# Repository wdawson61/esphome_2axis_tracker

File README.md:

# Solar Tracker Complete System
## Dual-Axis Solar Tracker with Home Assistant Integration

**Version**: 1.0.0  
**Date**: November 2024  
**Hardware**: ESP32-C6 + WitMotion HWT905 + BTS7960 Motor Drivers

---

## 📦 What's Included

This complete package contains everything you need to build a professional dual-axis solar tracker:

### 🏠 Home Assistant Add-on
Professional Python application for intelligent tracking control:
- Astronomical sun position calculations
- 9-axis sensor fusion algorithms
- Dual-axis PID control
- Wind monitoring with Ecowitt integration
- Web dashboard and MQTT interface
- **Location**: `home_assistant_addon/solar_tracker/`

### 🔧 ESP32-C6 Firmware
Hardware controller for motors and sensors:
- WitMotion HWT905 IMU via RS485/Modbus
- BTS7960 43A motor driver control (4 PWM outputs)
- Dual-axis motion control (azimuth + elevation)
- Limit switch protection
- HTTP API for Home Assistant
- **Location**: `firmware/Solar_Tracker_ESP32C6_HWT905.ino`

### 📚 Complete Documentation
Detailed guides for every aspect:
- Hardware setup and wiring
- Firmware configuration and upload
- Home Assistant installation
- PID tuning and calibration
- Troubleshooting and maintenance
- **Location**: `docs/`

### 🔬 Example Code
Additional firmware options and references:
- Generic ESP32 firmware (non-C6 boards)
- ESPHome configuration
- Modbus communication examples
- **Location**: `examples/`

---

## 🎯 Your Hardware Configuration

### Core Components
- **MCU**: Seeed XIAO ESP32-C6
- **IMU**: WitMotion HWT905 (9-axis, RS485)
- **Motor Drivers**: 2× BTS7960 43A H-Bridge
- **Motors**: 
  - Azimuth: Slewing drive
  - Elevation: Linear actuator
- **Sensors**: 2× limit switches (East/West)
- **Weather**: Ecowitt WS90 (integrated in Home Assistant)

### Pin Configuration Summary
```
RS485:  D4(TX), D5(RX), D2(DE)
Azimuth Motor:  D8(RPWM), D9(LPWM)
Elevation Motor: D10(RPWM), D1(LPWM)
Limits: D6(East), D7(West)
```

Full details in: `docs/ESP32C6_HWT905_BTS7960_SETUP.md`

---

## 🚀 Quick Start Guide

### 1. Upload ESP32 Firmware (30 minutes)
```bash
1. Install Arduino IDE 2.x
2. Add ESP32 board support
3. Install ArduinoJson library
4. Open: firmware/Solar_Tracker_ESP32C6_HWT905.ino
5. Configure WiFi credentials
6. Select Board: XIAO_ESP32C6
7. Upload
8. Note IP address from Serial Monitor
```

**Detailed guide**: `docs/ESP32C6_HWT905_BTS7960_SETUP.md`

### 2. Wire Hardware (2-4 hours)
```bash
1. Connect RS485 board to HWT905 IMU
2. Wire BTS7960 driver #1 to azimuth motor
3. Wire BTS7960 driver #2 to elevation motor
4. Install limit switches
5. Connect power supplies (12-24V motors, 5V ESP32)
```

**Wiring diagrams**: `docs/ESP32C6_HWT905_BTS7960_SETUP.md` and `docs/WIRING.md`

### 3. Install Home Assistant Add-on (20 minutes)
```bash
1. Install Mosquitto MQTT broker (if not already)
2. Add this repository to Home Assistant
3. Install "Solar Tracker Controller" add-on
4. Configure:
   - ESP32 IP address
   - Your location (lat/long)
   - Ecowitt wind entities
   - PID parameters
5. Start add-on
```

**Detailed guide**: `home_assistant_addon/solar_tracker/INSTALL.md`

### 4. Test and Calibrate (1-2 hours)
```bash
1. Test IMU readings
2. Test motor movements
3. Verify limit switches
4. Configure wind monitoring
5. Calibrate sensors
6. Tune PID parameters
7. Test in manual mode
8. Enable auto mode
```

**Testing procedures**: `docs/ESP32C6_HWT905_BTS7960_SETUP.md`

---

## 📂 Directory Structure

```
solar_tracker_complete/
│
├── 📄 README.md                          ⭐ This file - Start here!
│
├── 📁 firmware/                          🔧 ESP32-C6 Firmware
│   └── Solar_Tracker_ESP32C6_HWT905.ino    Main firmware for your hardware
│
├── 📁 home_assistant_addon/              🏠 Home Assistant Add-on
│   └── solar_tracker/                      Complete add-on directory
│       ├── solar_tracker/                  Python application
│       │   ├── main.py                     Entry point
│       │   ├── controller.py               Main control logic
│       │   ├── sensor_fusion.py            9-axis IMU fusion
│       │   ├── esp32_interface.py          ESP32 communication
│       │   ├── mqtt_interface.py           MQTT integration
│       │   ├── ha_interface.py             HA entity reading
│       │   └── web_server.py               Web dashboard
│       ├── web/                            Web interface
│       │   └── index.html                  Dashboard UI
│       ├── config.yaml                     Add-on configuration
│       ├── Dockerfile                      Container build
│       ├── requirements.txt                Dependencies
│       ├── run.sh                          Startup script
│       ├── README.md                       Complete documentation
│       ├── INSTALL.md                      Installation guide
│       ├── QUICKSTART.md                   Quick reference
│       ├── ECOWITT_SETUP.md                Ecowitt WS90 integration
│       ├── HA_ENTITY_INTEGRATION.md        Entity integration guide
│       └── CHANGELOG.md                    Version history
│
├── 📁 docs/                              📚 Documentation
│   ├── ESP32C6_HWT905_BTS7960_SETUP.md   ⭐ PRIMARY HARDWARE GUIDE
│   ├── INDEX.md                            Master file index
│   ├── PROJECT_SUMMARY.md                  Executive overview
│   ├── AUTOMATION_VS_ADDON.md              Comparison guide
│   ├── WIRING.md                           Detailed wiring info
│   └── HARDWARE_GUIDE.md                   General hardware info
│
└── 📁 examples/                          🔬 Reference Code
    ├── ESP32_Modbus_Web_Original.ino       Your original RS485 code
    ├── ESP32_Modbus_Web.ino                Enhanced Modbus interface
    ├── Solar_Tracker_ESP32_Hardware.ino    Generic ESP32 firmware
    └── solar_tracker_esphome.yaml          ESPHome alternative
```

---

## 📖 Documentation Guide

### 🚀 Getting Started
1. **Start Here**: `README.md` (this file)
2. **Hardware Setup**: `docs/ESP32C6_HWT905_BTS7960_SETUP.md`
3. **Add-on Installation**: `home_assistant_addon/solar_tracker/INSTALL.md`
4. **Daily Operation**: `home_assistant_addon/solar_tracker/QUICKSTART.md`

### 🔧 Configuration
- **Wind Integration**: `home_assistant_addon/solar_tracker/ECOWITT_SETUP.md`
- **PID Tuning**: `docs/ESP32C6_HWT905_BTS7960_SETUP.md` (Calibration section)
- **Wiring Details**: `docs/WIRING.md` and `docs/ESP32C6_HWT905_BTS7960_SETUP.md`

### 📊 Reference
- **Complete File Index**: `docs/INDEX.md`
- **Project Overview**: `docs/PROJECT_SUMMARY.md`
- **Design Decisions**: `docs/AUTOMATION_VS_ADDON.md`

---

## 🎯 Key Features

### Astronomical Tracking
✅ Real-time sun position calculation (< 0.01° accuracy)  
✅ Automatic timezone handling  
✅ Dawn-to-dusk operation  
✅ Configurable stow position  

### Sensor Fusion
✅ 9-axis IMU (accelerometer + gyroscope + magnetometer)  
✅ Complementary filter algorithm  
✅ Tilt-compensated compass heading  
✅ Temperature compensation  
✅ Drift-free orientation tracking  

### Motor Control
✅ Dual-axis PID control (azimuth + elevation)  
✅ Smooth motion with configurable parameters  
✅ Anti-windup and output limiting  
✅ BTS7960 43A H-bridge drivers  
✅ 4 separate PWM outputs  

### Safety Features
✅ Wind monitoring with auto-stow (Ecowitt WS90)  
✅ Configurable wind threshold (average or gust)  
✅ Hardware limit switches (East/West)  
✅ Emergency stop  
✅ Communication watchdog  
✅ Automatic night stowing  

### Integration
✅ Home Assistant MQTT auto-discovery  
✅ Real-time web dashboard  
✅ RESTful API  
✅ Ecowitt weather station integration  
✅ Cloud-free operation  

---

## ⚙️ System Requirements

### Home Assistant Server
- Home Assistant OS, Supervised, or Container
- 2GB+ RAM recommended
- Mosquitto MQTT broker add-on
- Network access to ESP32

### ESP32 Hardware
- XIAO ESP32-C6 (or compatible)
- 5V power supply (2A)
- WiFi 2.4GHz network
- Stable IP address recommended

### Motors and Drivers
- 12V or 24V DC motors
- BTS7960 motor drivers (2×)
- Power supply sized for motor current
- Proper heat sinking

---

## 🔍 Troubleshooting

### Common Issues

**ESP32 won't connect to WiFi**
- Check SSID/password in firmware
- Ensure 2.4GHz network (not 5GHz)
- Check Serial Monitor for errors

**No IMU data**
- Verify RS485 wiring (A-to-A, B-to-B)
- Check HWT905 power and baud rate
- Test with `curl http://ESP_IP/api/sensors`

**Motors don't move**
- Check BTS7960 power (12-24V)
- Verify enable pins (R_EN, L_EN to 5V)
- Test PWM outputs with multimeter/oscilloscope
- Check motor connections (M+, M-)

**Add-on can't connect to ESP32**
- Verify ESP32 IP address
- Test with: `curl http://ESP_IP/status`
- Check firewall rules
- Ensure ESP32 web server is running

**Full troubleshooting guide**: `docs/ESP32C6_HWT905_BTS7960_SETUP.md`

---

## 📊 Performance Specifications

### Tracking Accuracy
- **Positioning**: ±0.5° - 1° (with tuned PID)
- **IMU Resolution**: 0.01° (HWT905)
- **Update Rate**: 10Hz (sensor reading), 1Hz (control loop)

### Efficiency Gains
- **vs Fixed Panel**: +30-35% energy production
- **vs Single-Axis**: +5-10% additional gain
- **Total Improvement**: 35-45% over fixed installation

### Response Time
- **Sun Tracking**: 15°/hour average motion
- **Motor Speed**: Configurable via PID
- **Typical**: Full range in 2-5 minutes

---

## 🛠️ Maintenance

### Regular Checks (Monthly)
- [ ] Clean solar panels
- [ ] Inspect mechanical components
- [ ] Check wire connections
- [ ] Verify limit switches
- [ ] Test emergency stop
- [ ] Review tracking logs

### Seasonal Tasks
- [ ] Recalibrate IMU (if drift detected)
- [ ] Re-tune PID parameters (if needed)
- [ ] Lubricate moving parts
- [ ] Check weatherproofing
- [ ] Update firmware/add-on

---

## 🆘 Support

### Documentation
- All guides included in `docs/` directory
- Add-on documentation in `home_assistant_addon/solar_tracker/`
- Hardware-specific info in `docs/ESP32C6_HWT905_BTS7960_SETUP.md`

### Self-Help
1. Check relevant documentation first
2. Review troubleshooting sections
3. Examine add-on logs in Home Assistant
4. Check ESP32 Serial Monitor output
5. Test individual components

### Creating Issues
When reporting problems, include:
- Hardware configuration
- Firmware version
- Add-on configuration (remove passwords)
- Complete error logs
- Steps to reproduce
- Photos of wiring (if applicable)

---

## 🎓 Learning Path

### Beginner (Week 1)
1. Upload firmware and test basic operation
2. Get familiar with web interface
3. Test manual motor control
4. Install Home Assistant add-on

### Intermediate (Week 2-3)
1. Configure wind monitoring
2. Calibrate IMU sensors
3. Basic PID tuning
4. Enable auto tracking for short periods

### Advanced (Week 4+)
1. Fine-tune PID parameters
2. Optimize for your location
3. Set up automations
4. Monitor and analyze performance
5. Customize code if needed

---

## 📜 License

This project is provided as-is for educational and personal use.

**Components**:
- Custom code: MIT License (modify freely)
- Hardware designs: Open source
- Documentation: Creative Commons

**Third-party libraries**:
- ArduinoJson: MIT License
- Home Assistant: Apache 2.0 License
- See individual files for specific licenses

---

## 🙏 Acknowledgments

**Hardware**:
- Seeed Studio (XIAO ESP32-C6)
- WitMotion (HWT905 IMU)
- BTS7960 driver manufacturers

**Software**:
- Home Assistant community
- Arduino/ESP32 ecosystem
- Python libraries

**Inspiration**:
- DIY solar tracking community
- Open source hardware movement

---

## 📈 Future Enhancements

### Planned Features (v1.1+)
- [ ] Cloud cover detection
- [ ] Historical performance tracking
- [ ] Machine learning for predictive control
- [ ] Multi-tracker coordination
- [ ] Mobile app integration
- [ ] Weather forecast integration

### Community Contributions Welcome
- Additional hardware support
- Improved algorithms
- Better documentation
- Language translations

---

## 🎉 You're Ready to Build!

**What you have**:
✅ Professional dual-axis firmware  
✅ Intelligent Home Assistant add-on  
✅ Complete documentation  
✅ Hardware-specific setup guide  
✅ Troubleshooting resources  
✅ Example code and references  

**Time to build**: ~1-2 days for complete setup  
**Cost**: ~$300-500 for electronics + motors  
**Result**: Professional solar tracker with 35-45% efficiency gain!

---

## 📞 Quick Reference

| Component | Location | Purpose |
|-----------|----------|---------|
| **Firmware** | `firmware/Solar_Tracker_ESP32C6_HWT905.ino` | Upload to ESP32 |
| **Setup Guide** | `docs/ESP32C6_HWT905_BTS7960_SETUP.md` | Hardware instructions |
| **Add-on** | `home_assistant_addon/solar_tracker/` | Install in HA |
| **Install Guide** | `home_assistant_addon/solar_tracker/INSTALL.md` | HA setup |
| **Quick Ref** | `home_assistant_addon/solar_tracker/QUICKSTART.md` | Daily operation |
| **Wind Setup** | `home_assistant_addon/solar_tracker/ECOWITT_SETUP.md` | Ecowitt config |
| **Examples** | `examples/` | Reference code |

---

**Happy Tracking! 🌞**

For the most up-to-date information, always refer to the documentation in the `docs/` directory.

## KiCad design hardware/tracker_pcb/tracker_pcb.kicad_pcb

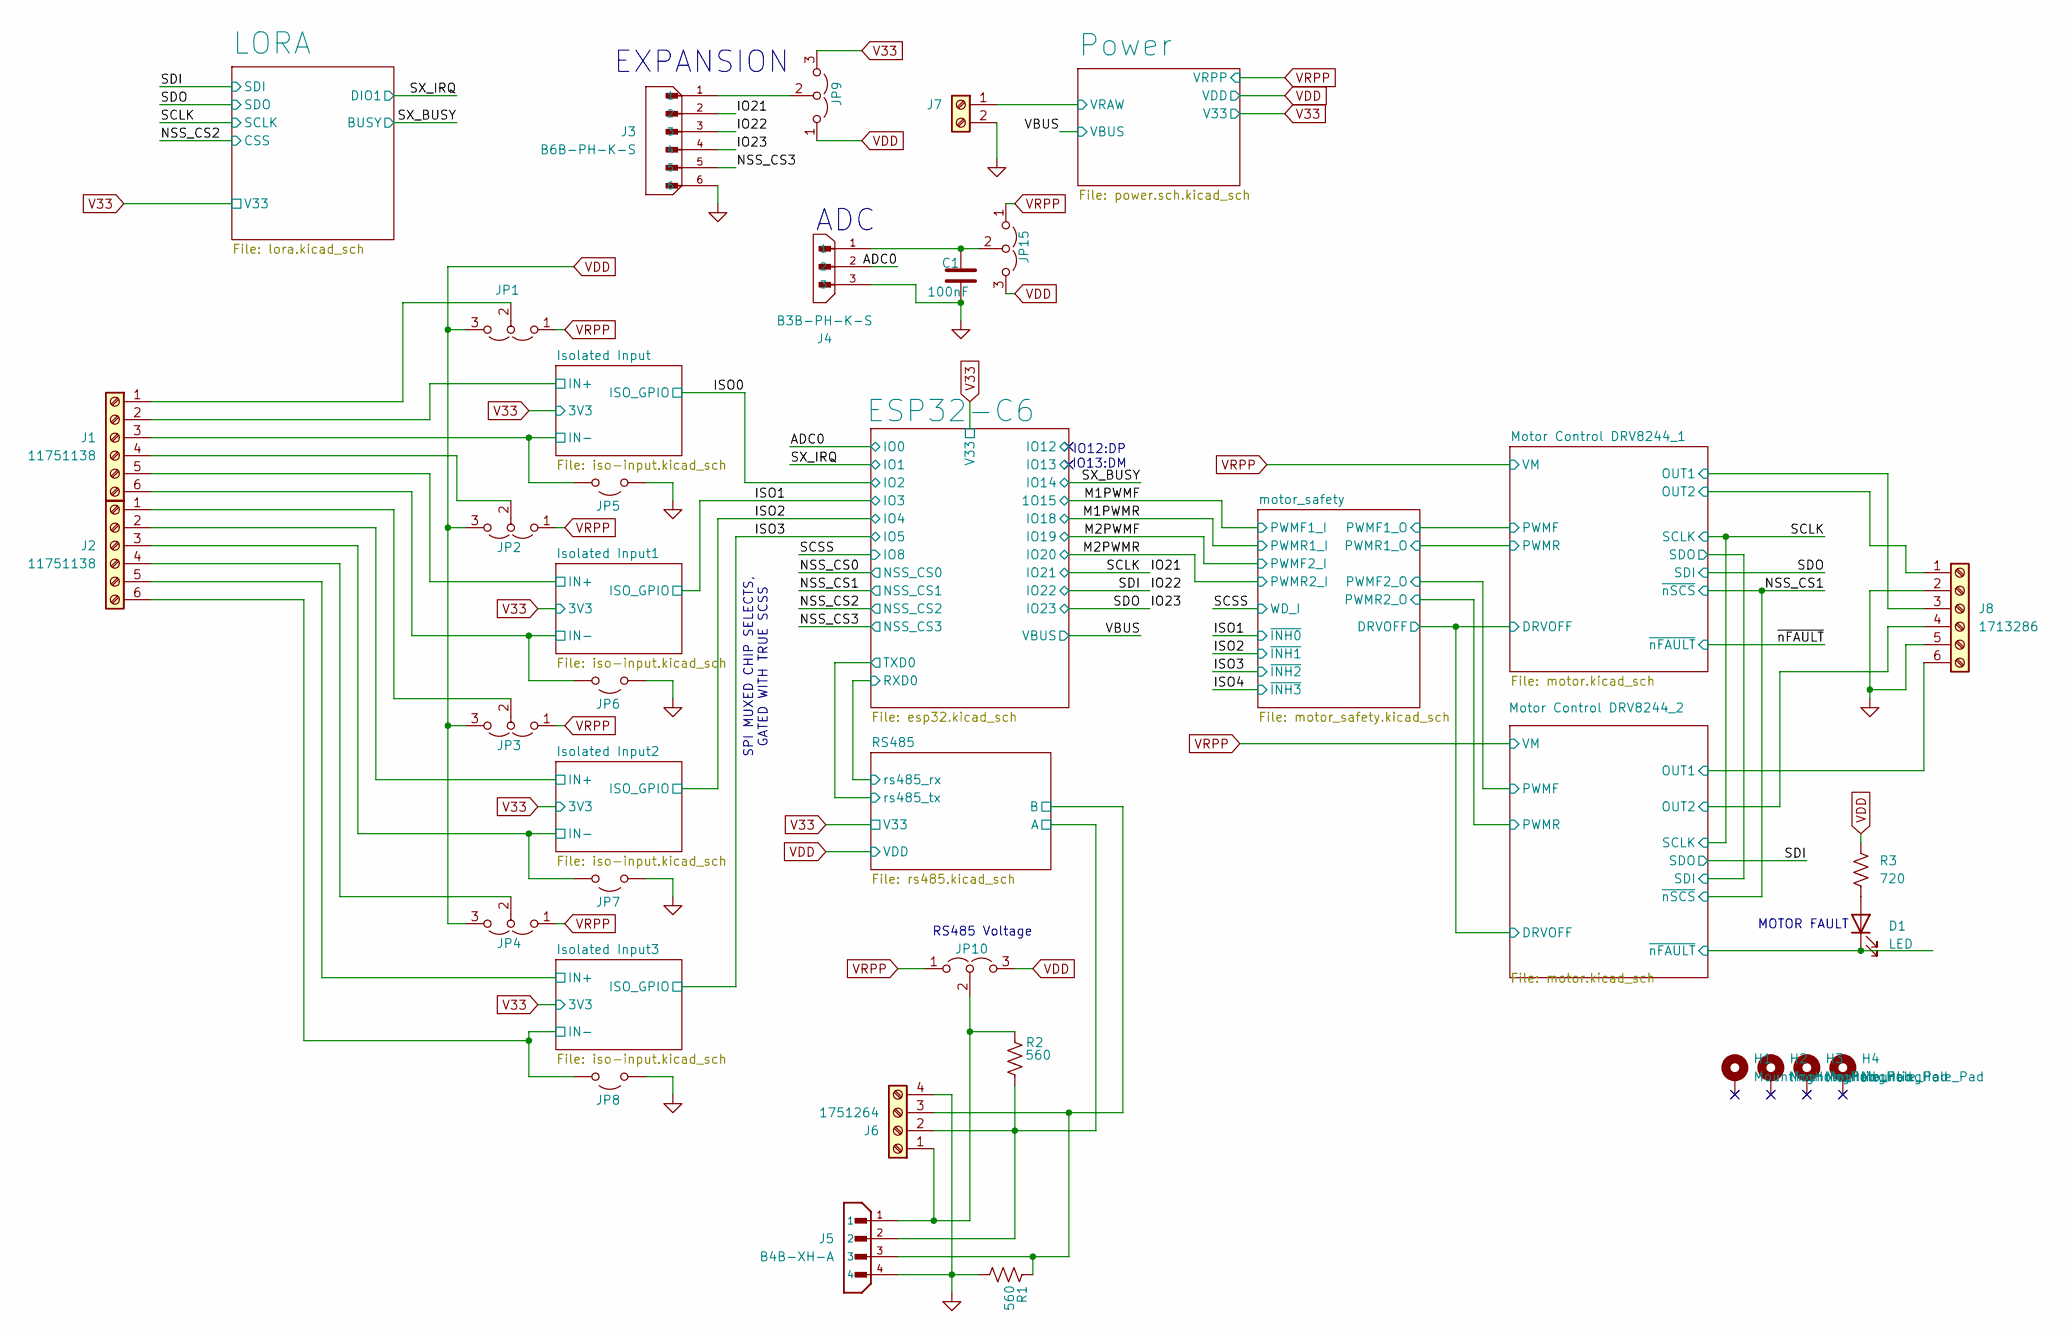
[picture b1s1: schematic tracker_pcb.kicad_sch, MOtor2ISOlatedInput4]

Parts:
C1: 100nF; C_0402_1005Metric; LCSC C1525
D1: LED; LED_0603_1608Metric; LCSC C12624
H1, H2, H3, H4: MountingHole_Pad; MountingHole_3.5mm_Pad_Via
J1, J2: 11751138; CONN_1751138_PXC; LCSC C2997513
J3: B6B-PH-K-S; JST_B6B-PH-K-S; LCSC C131342
J4: B3B-PH-K-S; JST_B3B-PH-K-S
J5: B4B-XH-A; JST_B4B-XH-A; PARTREV 7/4/21
J6: 1751264; PHOENIX_1751264; LCSC C99845
J7: Screw_Terminal_01x02; CONN_1720033_PXC; LCSC C5137859
J8: 1713286; PHOENIX_1905120; LCSC C2997523
JP1, JP2, JP3, JP4, JP9, JP10, JP15: Jumper_3_Open; PinHeader_1x03_P2.00mm_Vertical; LCSC C265013
JP5, JP6, JP7, JP8: Jumper_2_Open; PinHeader_1x02_P2.00mm_Vertical; LCSC C160332
R1, R2: 560; R_0603_1608Metric
R3: 720; R_0603_1608Metric; LCSC C23179

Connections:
/ADC0: J4.2; also elsewhere on the board
/IO21: J3.2; also elsewhere on the board
/IO22: J3.3; also elsewhere on the board
/IO23: J3.4; also elsewhere on the board
/Isolated Input1/IN+: J1.5; also elsewhere on the board
/Isolated Input1/IN-: J1.6, JP6.2 (B); also elsewhere on the board
/Isolated Input2/IN+: J2.2; also elsewhere on the board
/Isolated Input2/IN-: J2.3, JP7.2 (B); also elsewhere on the board
/Isolated Input3/IN+: J2.5; also elsewhere on the board
/Isolated Input3/IN-: J2.6, JP8.2 (B); also elsewhere on the board
/Isolated Input/IN+: J1.2; also elsewhere on the board
/Isolated Input/IN-: J1.3, JP5.2 (B); also elsewhere on the board
/Motor Control DRV8244_1/OUT1: J8.3; also elsewhere on the board
/Motor Control DRV8244_1/OUT2: J8.1; also elsewhere on the board
/Motor Control DRV8244_2/OUT1: J8.6; also elsewhere on the board
/Motor Control DRV8244_2/OUT2: J8.4; also elsewhere on the board
/Motor Control DRV8244_2/~nFAULT: D1.1 (K); also elsewhere on the board
/NSS_CS3: J3.5; also elsewhere on the board
/Power/VRAW: J7.1; also elsewhere on the board
/RS485/A: J5.2, J6.2, R2.1; also elsewhere on the board
/RS485/B: J5.3, J6.3, R1.2; also elsewhere on the board
GND: C1.2, J3.6, J4.3, J5.4, J6.4, J7.2, J8.2, J8.5, JP5.1 (A), JP6.1 (A), JP7.1 (A), JP8.1 (A), R1.1; also elsewhere on the board
unnamed: D1.2 (A), R3.1
unnamed: J1.1, JP1.2 (C)
unnamed: J1.4, JP2.2 (C)
unnamed: J2.1, JP3.2 (C)
unnamed: J2.4, JP4.2 (C)
unnamed: J3.1, JP9.2 (C)
unnamed: J5.1, J6.1, JP10.2 (C), R2.2
unnamed: C1.1, J4.1, JP15.2 (C)
V33: JP9.3 (B); also elsewhere on the board
VDD: JP1.3 (B), JP2.3 (B), JP3.3 (B), JP4.3 (B), JP9.1 (A), JP10.3 (B), JP15.3 (B), R3.2; also elsewhere on the board
VRPP: JP1.1 (A), JP2.1 (A), JP3.1 (A), JP4.1 (A), JP10.1 (A), JP15.1 (A); also elsewhere on the board

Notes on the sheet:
SPI MUXED CHIP SELECTS, GATED WITH TRUE SCSS
MOTOR FAULT
RS485 Voltage
IO12:DP IO13:DM
EXPANSION
ADC

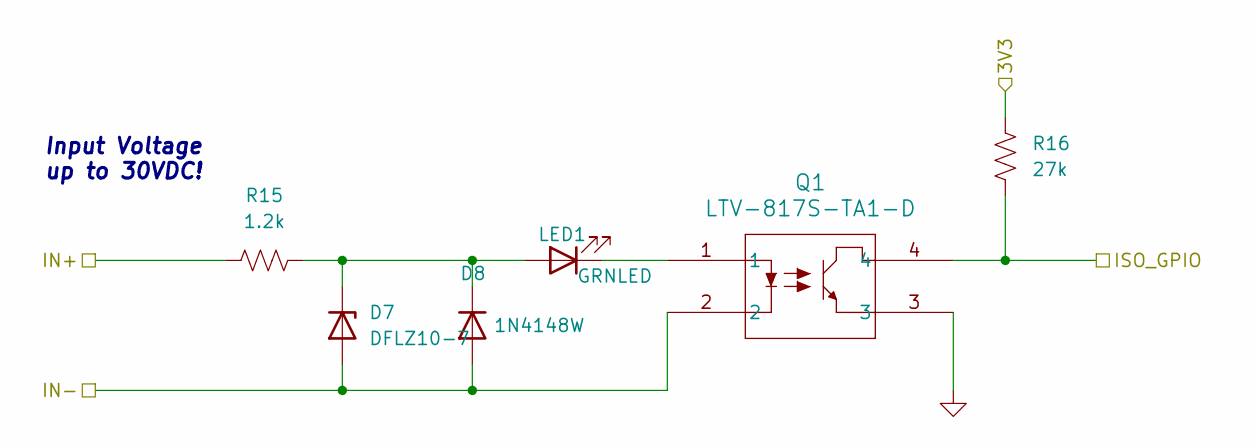
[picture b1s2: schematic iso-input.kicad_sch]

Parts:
D7: DFLZ10-7; DFLZ107; LCSC Part Name DFLZ10-7
D8: 1N4148W; D_SOD-323; LCSC C81598
LED1: GRNLED; LED_0603_1608Metric; LCSC C2288
Q1: LTV-817S-TA1-D; LTV-817S_LTO; LCSC C114603
R15: 1.2k; R_2010_5025Metric; LCSC C2078103
R16: 27k; R_0603_1608Metric; LCSC C22967

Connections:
/ISO0: Q1.4, R16.2; also elsewhere on the board
/Isolated Input/IN+: R15.1; also elsewhere on the board
/Isolated Input/IN-: D7.2 (A), D8.2 (A), Q1.2; also elsewhere on the board
GND: Q1.3; also elsewhere on the board
unnamed: D7.1 (K), D8.1 (K), LED1.2 (A), R15.2
unnamed: LED1.1 (K), Q1.1
V33: R16.1; also elsewhere on the board

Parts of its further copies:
D9, D11, D13: DFLZ10-7; DFLZ107; LCSC Part Name DFLZ10-7
D10, D12, D14: 1N4148W; D_SOD-323; LCSC C81598
LED2, LED3, LED4: GRNLED; LED_0603_1608Metric; LCSC C2288
Q2, Q3, Q4: LTV-817S-TA1-D; LTV-817S_LTO; LCSC C114603
R17, R19, R21: 1.2k; R_2010_5025Metric; LCSC C2078103
R18, R20, R22: 27k; R_0603_1608Metric; LCSC C22967

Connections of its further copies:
/ISO1: Q2.4, R18.2; also elsewhere on the board
/ISO2: Q3.4, R20.2; also elsewhere on the board
/ISO3: Q4.4, R22.2; also elsewhere on the board
/Isolated Input1/IN+: R17.1; also elsewhere on the board
/Isolated Input1/IN-: D9.2 (A), D10.2 (A), Q2.2; also elsewhere on the board
/Isolated Input2/IN+: R19.1; also elsewhere on the board
/Isolated Input2/IN-: D11.2 (A), D12.2 (A), Q3.2; also elsewhere on the board
/Isolated Input3/IN+: R21.1; also elsewhere on the board
/Isolated Input3/IN-: D13.2 (A), D14.2 (A), Q4.2; also elsewhere on the board
GND: Q2.3, Q3.3, Q4.3; also elsewhere on the board
unnamed: D9.1 (K), D10.1 (K), LED2.2 (A), R17.2
unnamed: D11.1 (K), D12.1 (K), LED3.2 (A), R19.2
unnamed: D13.1 (K), D14.1 (K), LED4.2 (A), R21.2
unnamed: LED2.1 (K), Q2.1
unnamed: LED3.1 (K), Q3.1
unnamed: LED4.1 (K), Q4.1
V33: R18.1, R20.1, R22.1; also elsewhere on the board

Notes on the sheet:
Input Voltage up to 30VDC!

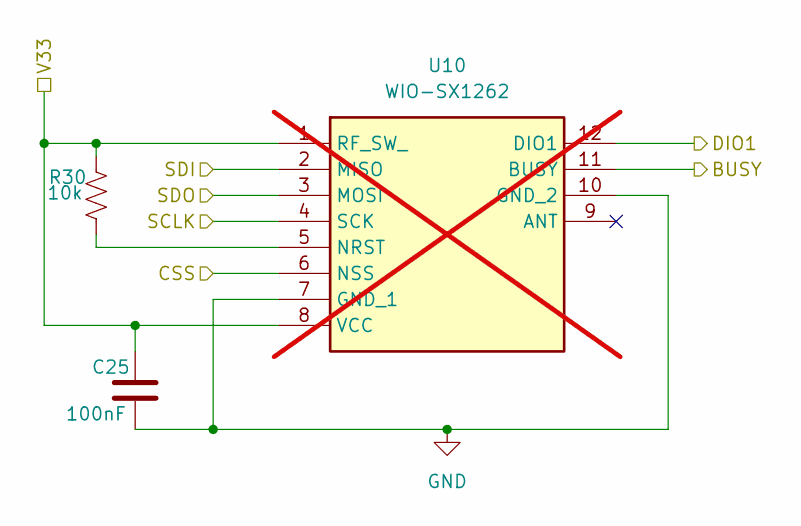
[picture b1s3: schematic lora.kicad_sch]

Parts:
C25: 100nF; C_0603_1608Metric; LCSC C1590
R30: 10k; R_0805_2012Metric; LCSC C17414
U10: WIO-SX1262; 114993390; Mouser Part Number 713-114993390; not fitted

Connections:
/IO21: U10.4 (SCK); also elsewhere on the board
/IO22: U10.2 (MISO); also elsewhere on the board
/IO23: U10.3 (MOSI); also elsewhere on the board
/NSS_CS2: U10.6 (NSS); also elsewhere on the board
/SX_BUSY: U10.11 (BUSY); also elsewhere on the board
/SX_IRQ: U10.12 (DIO1); also elsewhere on the board
GND: C25.2, U10.7 (GND_1), U10.10 (GND_2); also elsewhere on the board
unnamed: R30.2, U10.5 (NRST)
V33: C25.1, R30.1, U10.1 (RF_SW_), U10.8 (VCC); also elsewhere on the board

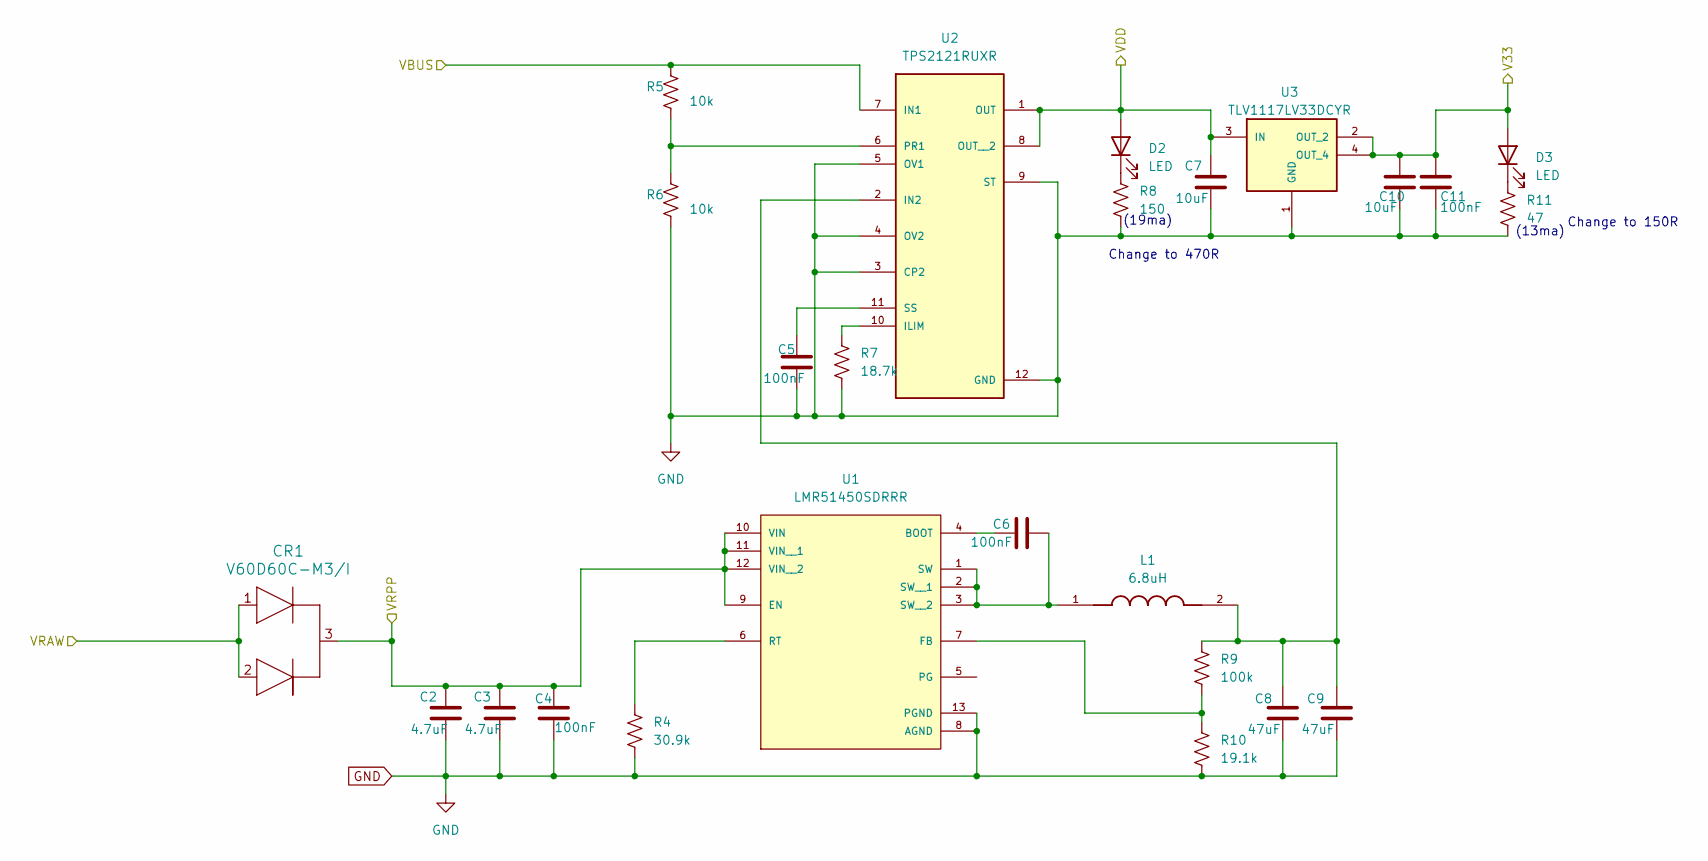
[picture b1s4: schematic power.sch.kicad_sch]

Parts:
C2, C3: 4.7uF; C_1206_3216Metric; LCSC C77096
C4, C6, C11: 100nF; C_0603_1608Metric; LCSC C1590
C5: 100nF; C_0402_1005Metric; LCSC C1525
C7, C10: 10uF; C_1206_3216Metric; LCSC C1849
C8, C9: 47uF; C_1210_3225Metric; LCSC C77101
CR1: V60D60C-M3/I; DPAK_60C-M3&slash_I_VIS; LCSC C3759778
D2, D3: LED; LED_0603_1608Metric; LCSC C12624
L1: 6.8uH; IND_XAL6060-682MEC; PARTREV 11/02/18; LCSC C5355913
R4: 30.9k; R_0603_1608Metric; LCSC C23022
R5, R6: 10k; R_0402_1005Metric; LCSC C25744
R7: 18.7k; R_0402_1005Metric; LCSC C11476
R8: 150; R_0603_1608Metric; LCSC C22808
R9: 100k; R_0603_1608Metric; LCSC C844916
R10: 19.1k; R_0603_1608Metric; LCSC C844132
R11: 47; R_0603_1608Metric; LCSC C1211
U1: LMR51450SDRRR; CONV_LMR51450SDRRR; PARTREV December 2022; LCSC C6890985
U2: TPS2121RUXR; IC_TPS2121RUXR; LCSC C485916
U3: TLV1117LV33DCYR; VREG_TLV1117LV33DCYR; PARTREV B; LCSC C15578

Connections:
/Power/VRAW: CR1.1, CR1.2; also elsewhere on the board
/VBUS: R5.2, U2.7 (IN1); also elsewhere on the board
GND: C2.2, C3.2, C4.2, C5.2, C7.2, C8.2, C9.2, C10.2, C11.2, R4.1, R6.1, R7.1, R8.1, R10.1, R11.1, U1.8 (AGND), U1.13 (PGND), U2.3 (CP2), U2.4 (OV2), U2.5 (OV1), U2.9 (ST), U2.12 (GND), U3.1 (GND); also elsewhere on the board
unnamed: D2.1 (K), R8.2
unnamed: D3.1 (K), R11.2
unnamed: C6.1, U1.4 (BOOT)
unnamed: R9.1, R10.2, U1.7 (FB)
unnamed: R4.2, U1.6 (RT)
unnamed: C6.2, L1.1, U1.1 (SW), U1.2 (SW__1), U1.3 (SW__2)
unnamed: R7.2, U2.10 (ILIM)
unnamed: C8.1, C9.1, L1.2, R9.2, U2.2 (IN2)
unnamed: R5.1, R6.2, U2.6 (PR1)
unnamed: C5.1, U2.11 (SS)
V33: C10.1, C11.1, D3.2 (A), U3.2 (OUT_2), U3.4 (OUT_4); also elsewhere on the board
VDD: C7.1, D2.2 (A), U2.1 (OUT), U2.8 (OUT__2), U3.3 (IN); also elsewhere on the board
VRPP: C2.1, C3.1, C4.1, CR1.3, U1.9 (EN), U1.10 (VIN), U1.11 (VIN__1), U1.12 (VIN__2); also elsewhere on the board

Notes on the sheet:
Change to 470R
(13ma)
(19ma)
Change to 150R

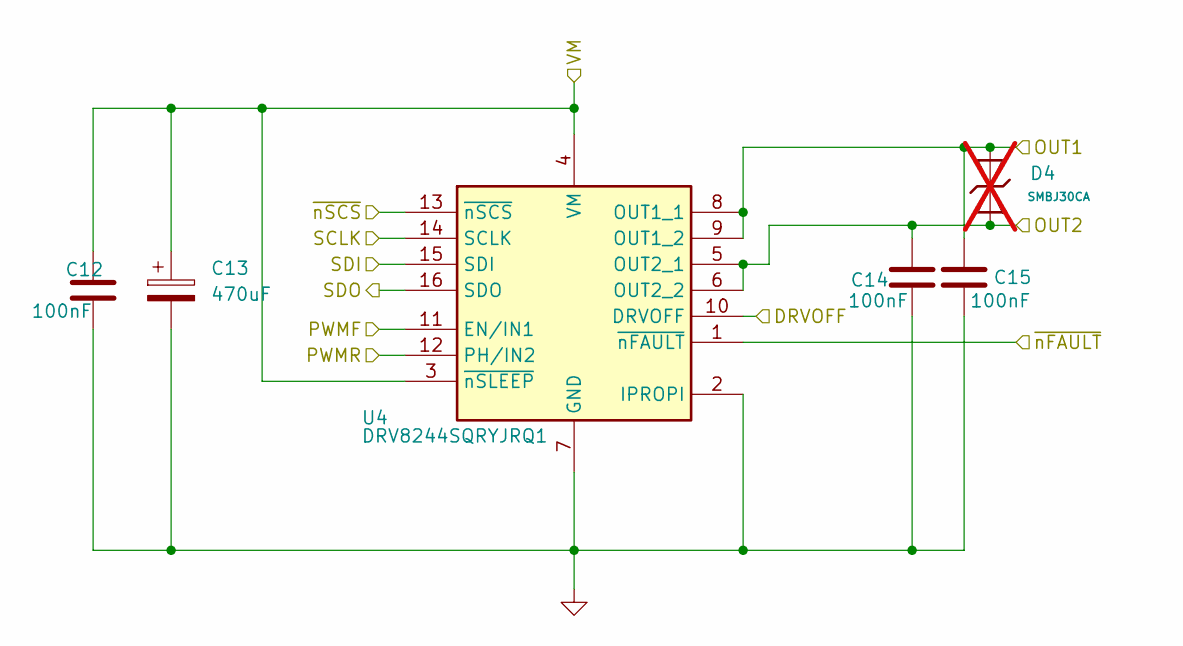
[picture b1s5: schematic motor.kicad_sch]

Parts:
C12, C14, C15: 100nF; C_0603_1608Metric; LCSC C1590
C13: 470uF; CP_Elec_18x17.5; LCSC C688951
D4: SMBJ30CA; D_SMB; Clamping Voltage 48.4V; Voltage - Breakdown 36.8V; Part SMBJ30CA; LCSC C19077585; not fitted
U4: DRV8244SQRYJRQ1; DRV8244HQRYJRQ1; Mouser Part Number 595-DRV8244HQRYJRQ1

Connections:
/IO21: U4.14 (SCLK); also elsewhere on the board
/IO23: U4.15 (SDI); also elsewhere on the board
/Motor Control DRV8244_1/DRVOFF: U4.10 (DRVOFF); also elsewhere on the board
/Motor Control DRV8244_1/OUT1: C15.1, D4.2, U4.8 (OUT1_1), U4.9 (OUT1_2); also elsewhere on the board
/Motor Control DRV8244_1/OUT2: C14.1, D4.1, U4.5 (OUT2_1), U4.6 (OUT2_2); also elsewhere on the board
/Motor Control DRV8244_1/PWMF: U4.11 (EN/IN1); also elsewhere on the board
/Motor Control DRV8244_1/PWMR: U4.12 (PH/IN2); also elsewhere on the board
/Motor Control DRV8244_1/SDO: U4.16 (SDO); also elsewhere on the board
/NSS_CS1: U4.13 (~nSCS); also elsewhere on the board
/~nFAULT: U4.1 (~nFAULT)
GND: C12.2, C13.2, C14.2, C15.2, U4.2 (IPROPI), U4.7 (GND); also elsewhere on the board
VRPP: C12.1, C13.1, U4.3 (~nSLEEP), U4.4 (VM); also elsewhere on the board

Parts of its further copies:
C16, C18, C19: 100nF; C_0603_1608Metric; LCSC C1590
C17: 470uF; CP_Elec_18x17.5; LCSC C688951
D5: SMBJ30CA; D_SMB; Clamping Voltage 48.4V; Voltage - Breakdown 36.8V; Part SMBJ30CA; LCSC C19077585; not fitted
U5: DRV8244SQRYJRQ1; DRV8244HQRYJRQ1; Mouser Part Number 595-DRV8244HQRYJRQ1

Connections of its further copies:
/IO21: U5.14 (SCLK); also elsewhere on the board
/IO22: U5.16 (SDO); also elsewhere on the board
/Motor Control DRV8244_1/DRVOFF: U5.10 (DRVOFF); also elsewhere on the board
/Motor Control DRV8244_1/SDO: U5.15 (SDI); also elsewhere on the board
/Motor Control DRV8244_2/OUT1: C19.1, D5.2, U5.8 (OUT1_1), U5.9 (OUT1_2); also elsewhere on the board
/Motor Control DRV8244_2/OUT2: C18.1, D5.1, U5.5 (OUT2_1), U5.6 (OUT2_2); also elsewhere on the board
/Motor Control DRV8244_2/PWMF: U5.11 (EN/IN1); also elsewhere on the board
/Motor Control DRV8244_2/PWMR: U5.12 (PH/IN2); also elsewhere on the board
/Motor Control DRV8244_2/~nFAULT: U5.1 (~nFAULT); also elsewhere on the board
/NSS_CS1: U5.13 (~nSCS); also elsewhere on the board
GND: C16.2, C17.2, C18.2, C19.2, U5.2 (IPROPI), U5.7 (GND); also elsewhere on the board
VRPP: C16.1, C17.1, U5.3 (~nSLEEP), U5.4 (VM); also elsewhere on the board

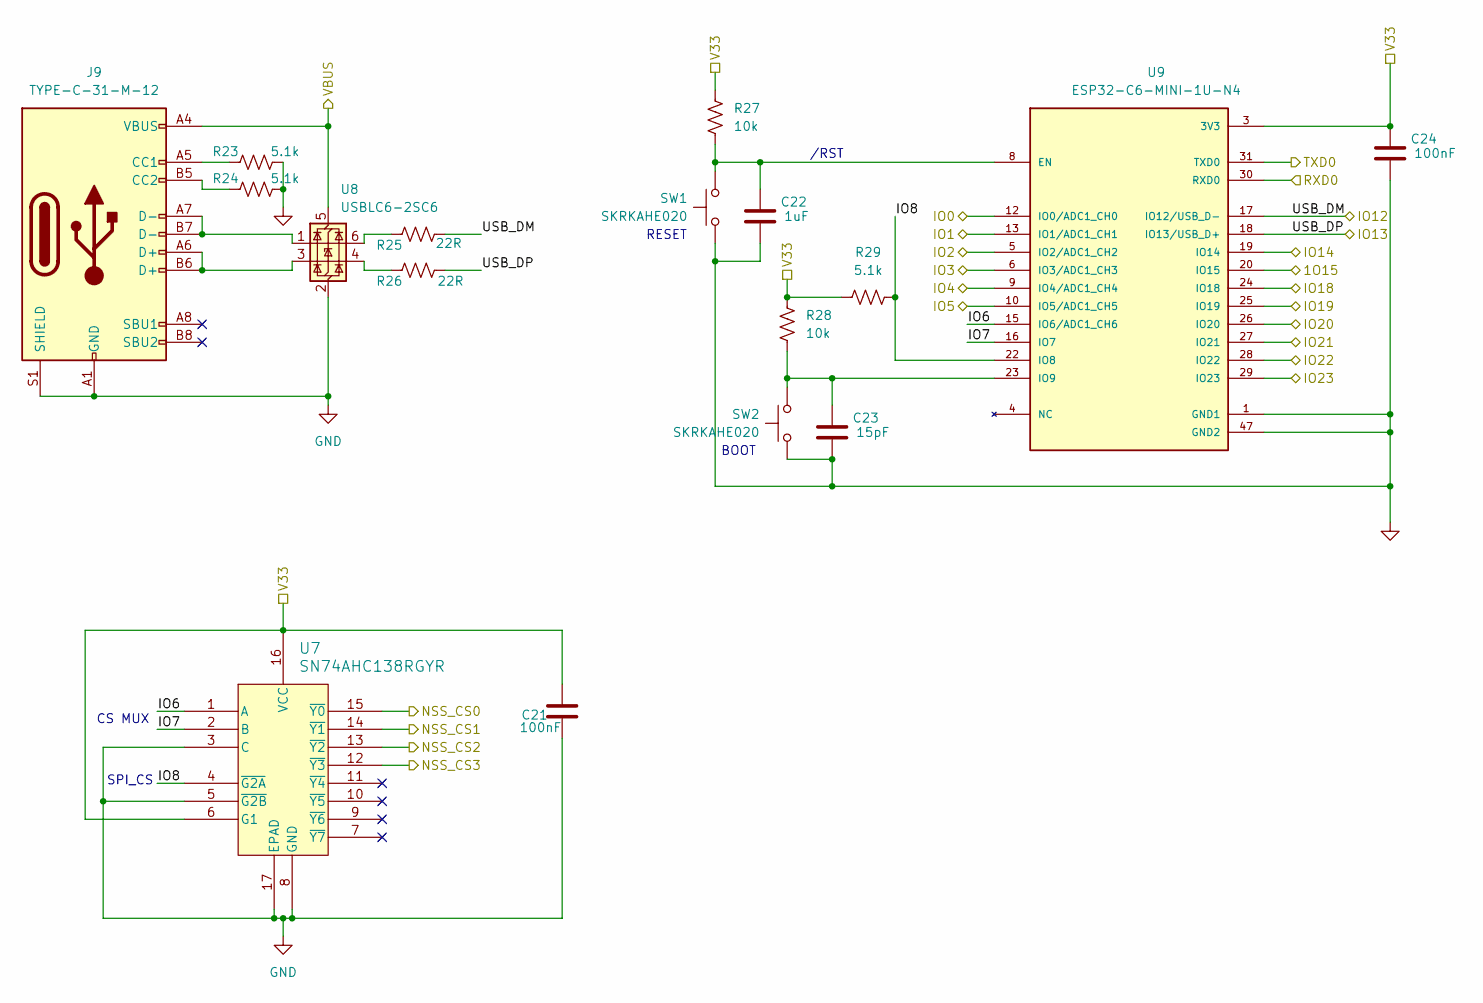
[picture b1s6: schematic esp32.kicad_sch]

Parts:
C21, C24: 100nF; C_0603_1608Metric; LCSC C1590
C22: 1uF; C_0603_1608Metric; LCSC C1591
C23: 15pF; C_0603_1608Metric; LCSC C1644
J9: TYPE-C-31-M-12; USB_C_Receptacle_HRO_TYPE-C-31-M-12; LCSC C165948
R23, R24, R29: 5.1k; R_0603_1608Metric; LCSC C23186
R25, R26: 22R; R_0603_1608Metric; LCSC C23345
R27, R28: 10k; R_0603_1608Metric; LCSC C25804
SW1, SW2: SKRKAHE020; SKRKAEE020; LCSC C493285
U7: SN74AHC138RGYR; RGY16_2P55X2P05
U8: USBLC6-2SC6; SOT-23-6; LCSC C7519
U9: ESP32-C6-MINI-1U-N4; XCVR_ESP32-C6-MINI-1U-N4; PARTREV 1.0; LCSC C20627095

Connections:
/ADC0: U9.12 (IO0/ADC1_CH0); also elsewhere on the board
/ESP32-C6/IO6: U7.1 (A), U9.15 (IO6/ADC1_CH6)
/ESP32-C6/IO7: U7.2 (B), U9.16 (IO7)
/ESP32-C6/IO8: R29.1, U7.4 (~G2A), U9.22 (IO8)
/ESP32-C6/RXD0: U9.30 (RXD0); also elsewhere on the board
/ESP32-C6/TXD0: U9.31 (TXD0); also elsewhere on the board
/ESP32-C6/USB_DM: R25.1, U9.17 (IO12/USB_D-)
/ESP32-C6/USB_DP: R26.1, U9.18 (IO13/USB_D+)
/IO21: U9.27 (IO21); also elsewhere on the board
/IO22: U9.28 (IO22); also elsewhere on the board
/IO23: U9.29 (IO23); also elsewhere on the board
/ISO0: U9.5 (IO2/ADC1_CH2); also elsewhere on the board
/ISO1: U9.6 (IO3/ADC1_CH3); also elsewhere on the board
/ISO2: U9.9 (IO4/ADC1_CH4); also elsewhere on the board
/ISO3: U9.10 (IO5/ADC1_CH5); also elsewhere on the board
/M1PWMF: U9.20 (IO15); also elsewhere on the board
/M1PWMR: U9.24 (IO18); also elsewhere on the board
/M2PWMF: U9.25 (IO19); also elsewhere on the board
/M2PWMR: U9.26 (IO20); also elsewhere on the board
/NSS_CS0: U7.15 (~Y0)
/NSS_CS1: U7.14 (~Y1); also elsewhere on the board
/NSS_CS2: U7.13 (~Y2); also elsewhere on the board
/NSS_CS3: U7.12 (~Y3); also elsewhere on the board
/SX_BUSY: U9.19 (IO14); also elsewhere on the board
/SX_IRQ: U9.13 (IO1/ADC1_CH1); also elsewhere on the board
/VBUS: J9.A4 (VBUS), J9.A9 (VBUS), J9.B4 (VBUS), J9.B9 (VBUS), U8.5 (VBUS); also elsewhere on the board
GND: C21.2, C22.2, C23.2, C24.2, J9.A1 (GND), J9.A12 (GND), J9.B1 (GND), J9.B12 (GND), J9.S1 (SHIELD), R23.1, R24.1, SW1.2, SW2.2, U7.3 (C), U7.5 (~G2B), U7.8 (GND), U7.17 (EPAD), U8.2 (GND), U9.1 (GND1), U9.2 (GND1), U9.11 (GND1), U9.14 (GND1), U9.36 (GND1), U9.37 (GND1), U9.38 (GND1), U9.39 (GND1), U9.40 (GND1), U9.41 (GND1), U9.42 (GND1), U9.43 (GND1), U9.44 (GND1), U9.45 (GND1), U9.46 (GND1), U9.47 (GND2), U9.48 (GND2), U9.49_1 (GND2), U9.49_2 (GND2), U9.49_3 (GND2), U9.49_4 (GND2), U9.49_5 (GND2), U9.49_6 (GND2), U9.49_7 (GND2), U9.49_8 (GND2), U9.49_9 (GND2), U9.50 (GND2), U9.51 (GND2), U9.52 (GND2), U9.53 (GND2); also elsewhere on the board
unnamed: J9.A5 (CC1), R23.2
unnamed: J9.B5 (CC2), R24.2
unnamed: J9.A6 (D+), J9.B6 (D+), U8.3 (I/O2)
unnamed: J9.A7 (D-), J9.B7 (D-), U8.1 (I/O1)
unnamed: R25.2, U8.6 (I/O1)
unnamed: R26.2, U8.4 (I/O2)
unnamed: C22.1, R27.1, SW1.1, U9.8 (EN)
unnamed: C23.1, R28.1, SW2.1, U9.23 (IO9)
V33: C21.1, C24.1, R27.2, R28.2, R29.2, U7.6 (G1), U7.16 (VCC), U9.3 (3V3); also elsewhere on the board

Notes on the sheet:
SPI_CS
BOOT
RESET
/RST
CS MUX

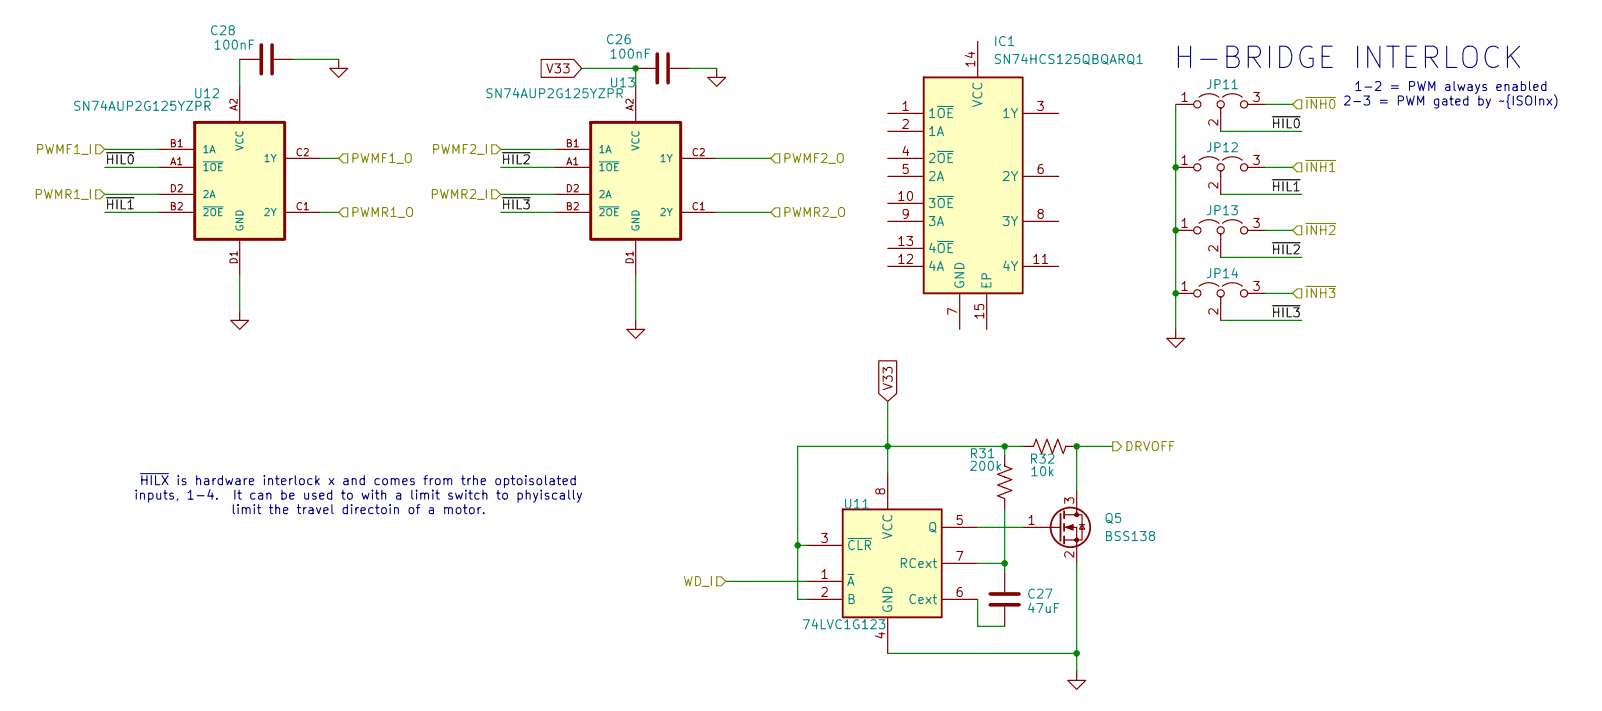
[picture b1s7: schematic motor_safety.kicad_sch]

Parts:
C26, C28: 100nF; C_0603_1608Metric; LCSC C1590
C27: 47uF; C_0805_2012Metric; LCSC C77072
IC1: SN74HCS125QBQARQ1; Mouser Part Number 595-N74HCS125QBQARQ1
JP11, JP12, JP13, JP14: Jumper_3_Open; PinHeader_1x03_P2.00mm_Vertical; LCSC C265013
Q5: BSS138; SOT-23
R31: 200k; R_0603_1608Metric
R32: 10k; R_0603_1608Metric; LCSC C25804
U11: 74LVC1G123; 74LVC1G123GN115
U12, U13: SN74AUP2G125YZPR; YZP8; LCSC C2676075

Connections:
/ISO1: JP11.3 (B); also elsewhere on the board
/ISO2: JP12.3 (B); also elsewhere on the board
/ISO3: JP13.3 (B); also elsewhere on the board
/ISO4: JP14.3 (B)
/M1PWMF: U12.B1 (1A); also elsewhere on the board
/M1PWMR: U12.D2 (2A); also elsewhere on the board
/M2PWMF: U13.B1 (1A); also elsewhere on the board
/M2PWMR: U13.D2 (2A); also elsewhere on the board
/Motor Control DRV8244_1/DRVOFF: Q5.3 (D), R32.1; also elsewhere on the board
/Motor Control DRV8244_1/PWMF: U12.C2 (1Y); also elsewhere on the board
/Motor Control DRV8244_1/PWMR: U12.C1 (2Y); also elsewhere on the board
/Motor Control DRV8244_2/PWMF: U13.C2 (1Y); also elsewhere on the board
/Motor Control DRV8244_2/PWMR: U13.C1 (2Y); also elsewhere on the board
/SCSS: U11.1 (~A)
/motor_safety/~HIL0: JP11.2 (C), U12.A1 (~1OE)
/motor_safety/~HIL1: JP12.2 (C), U12.B2 (~2OE)
/motor_safety/~HIL2: JP13.2 (C), U13.A1 (~1OE)
/motor_safety/~HIL3: JP14.2 (C), U13.B2 (~2OE)
GND: C26.2, C28.2, JP11.1 (A), JP12.1 (A), JP13.1 (A), JP14.1 (A), Q5.2 (S), U11.4 (GND), U12.D1 (GND), U13.D1 (GND); also elsewhere on the board
unnamed: Q5.1 (G), U11.5 (Q)
unnamed: C27.2, U11.6 (Cext)
unnamed: C27.1, R31.1, U11.7 (RCext)
unnamed: C28.1, U12.A2 (VCC)
V33: C26.1, R31.2, R32.2, U11.2 (B), U11.3 (~CLR), U11.8 (VCC), U13.A2 (VCC); also elsewhere on the board

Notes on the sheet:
1-2 = PWM always enabled 2-3 = PWM gated by ~{ISOInx)
~{HILX} is hardware interlock x and comes from trhe optoisolated inputs, 1-4. It can be used to with a limit switch to phyiscally limit the travel directoin of a motor.
H-BRIDGE INTERLOCK

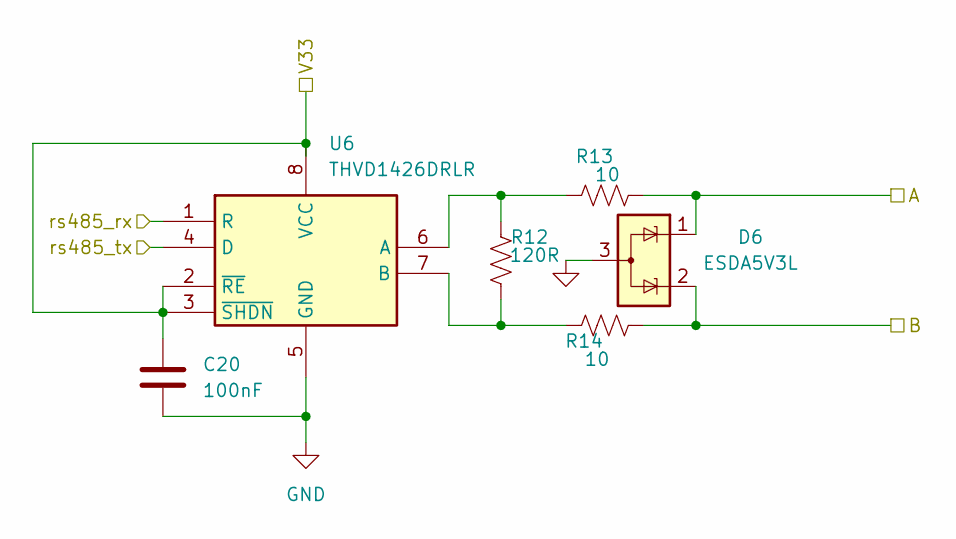
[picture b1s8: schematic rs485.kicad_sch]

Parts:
C20: 100nF; C_0603_1608Metric; LCSC C1590
D6: ESDA5V3L; SOT-23-3; LCSC C87911
R12: 120R; R_0603_1608Metric; LCSC C22787
R13, R14: 10; R_0805_2012Metric; LCSC C22859
U6: THVD1426DRLR; SOTFL50P160X60-8N; Mouser Part Number 595-THVD1426DRLR

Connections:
/ESP32-C6/RXD0: U6.1 (R); also elsewhere on the board
/ESP32-C6/TXD0: U6.4 (D); also elsewhere on the board
/RS485/A: D6.1 (K), R13.2; also elsewhere on the board
/RS485/B: D6.2 (K), R14.2; also elsewhere on the board
GND: C20.2, D6.3 (A), U6.5 (GND); also elsewhere on the board
unnamed: R12.2, R13.1, U6.6 (A)
unnamed: R12.1, R14.1, U6.7 (B)
V33: C20.1, U6.2 (~RE), U6.3 (~SHDN), U6.8 (VCC); also elsewhere on the board
